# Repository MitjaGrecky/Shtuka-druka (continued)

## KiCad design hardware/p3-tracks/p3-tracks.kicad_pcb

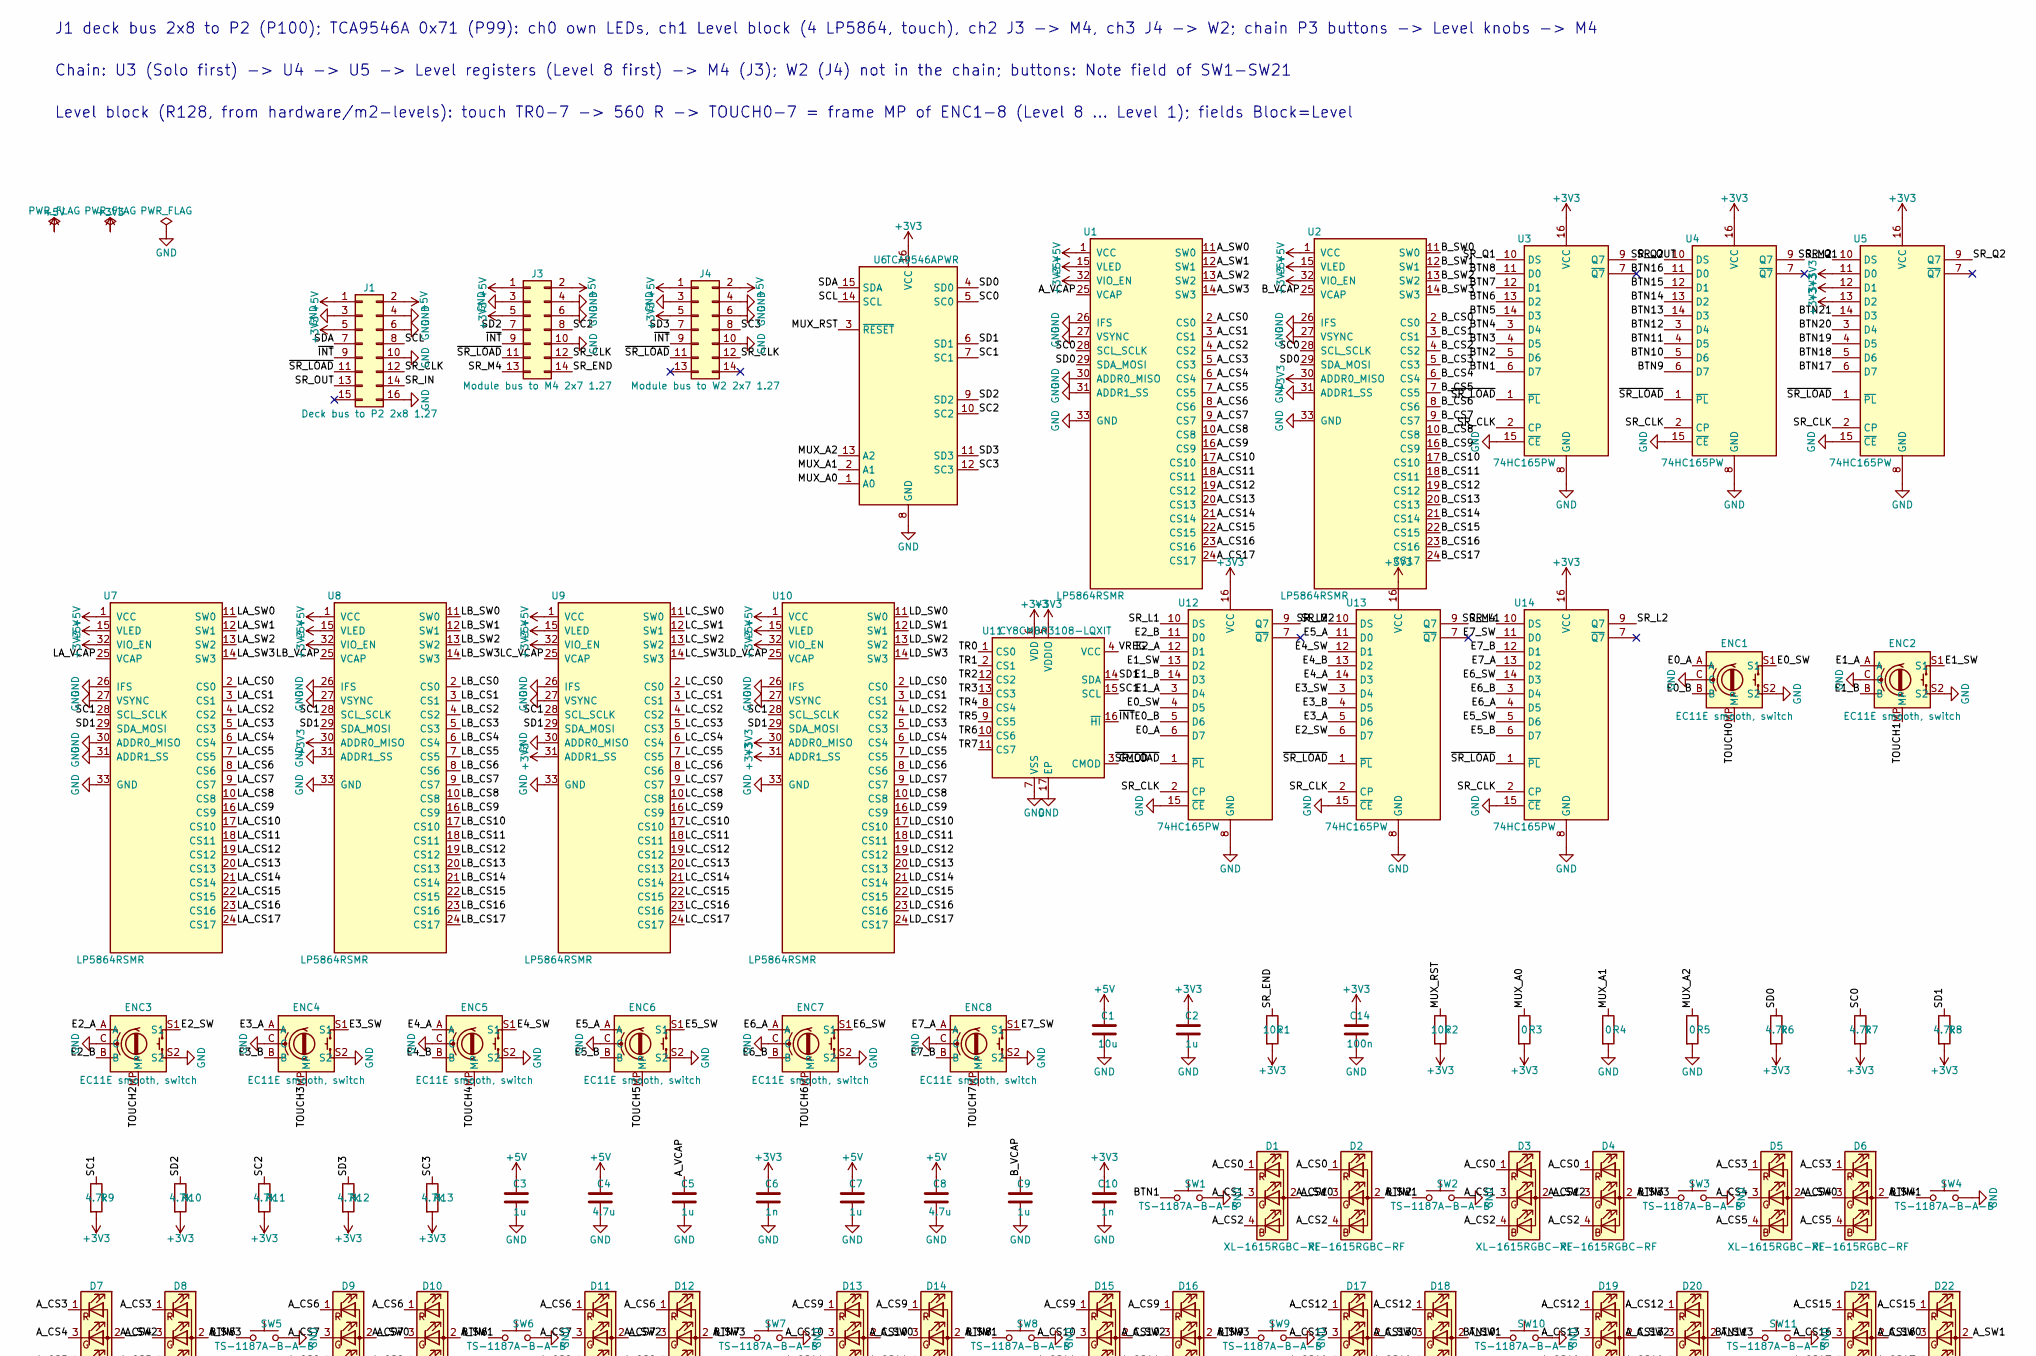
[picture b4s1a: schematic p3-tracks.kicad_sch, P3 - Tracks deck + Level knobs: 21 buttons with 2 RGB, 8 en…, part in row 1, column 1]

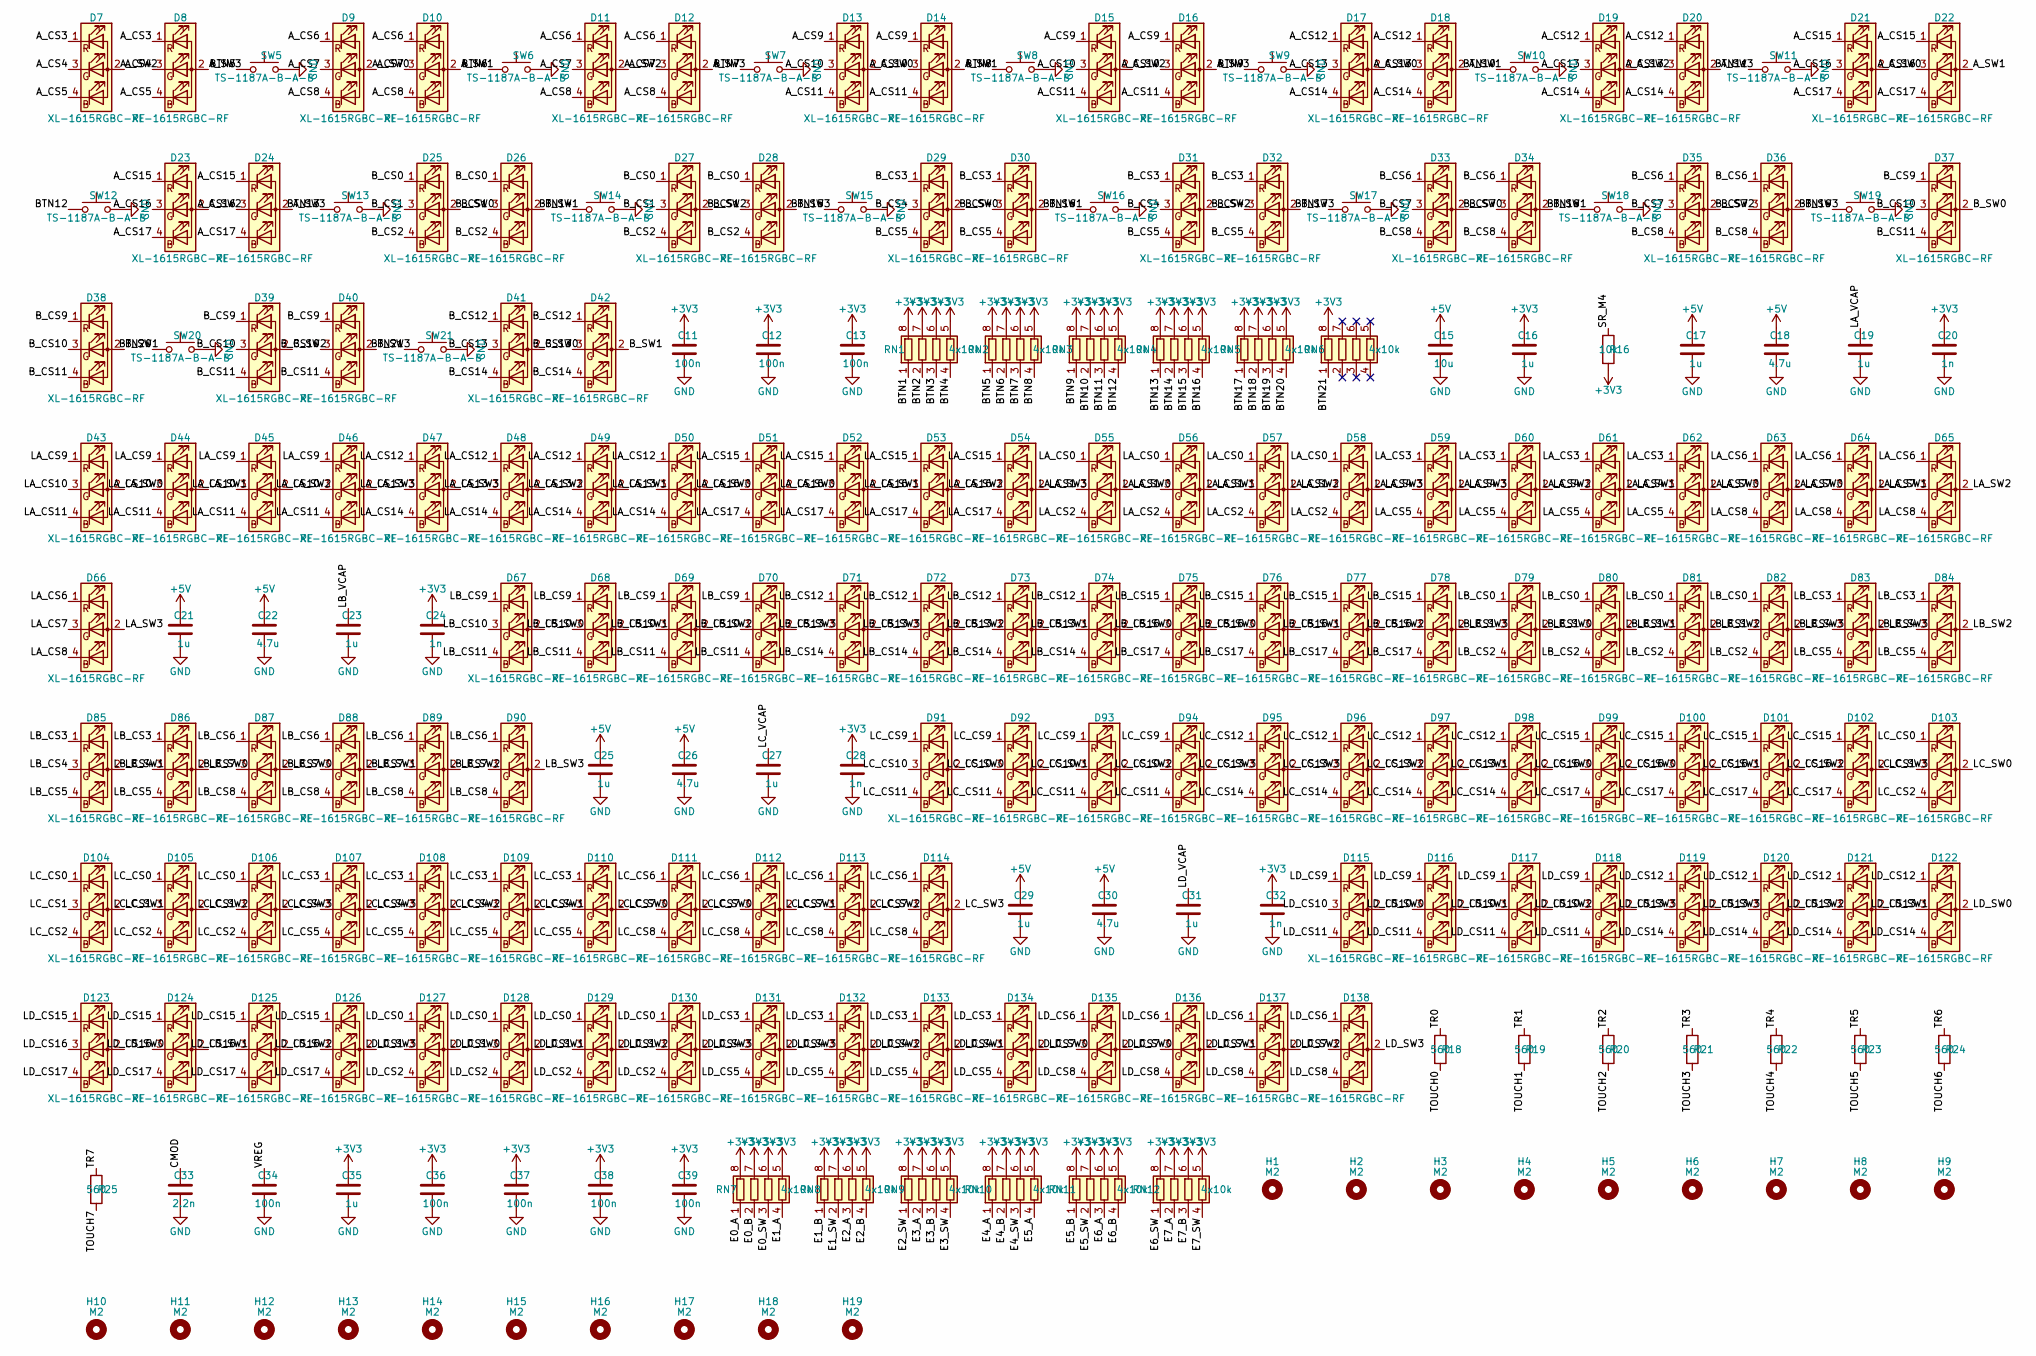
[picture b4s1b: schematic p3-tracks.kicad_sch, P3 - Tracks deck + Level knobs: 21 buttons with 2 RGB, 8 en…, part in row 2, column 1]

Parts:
C1, C15: 10u; C_0805_2012Metric; LCSC C15850
C2, C3, C5, C7, C9, C16, C17, C19, C21, C23, C25, C27, C29, C31, C35: 1u; C_0402_1005Metric; LCSC C52923
C4, C8, C18, C22, C26, C30: 4.7u; C_0805_2012Metric; LCSC C1779
C6, C10, C20, C24, C28, C32: 1n; C_0402_1005Metric; LCSC C1523
C11, C12, C13, C14, C34, C36, C37, C38, C39: 100n; C_0402_1005Metric; LCSC C1525
C33: 2.2n; C_0402_1005Metric; LCSC C1531
D1, D2, D3, D4, D5, D6, D7, D8, D9, D10, D11, D12, D13, D14, D15, D16, D17, D18, D19, D20, D21, D22, D23, D24, D25, D26, D27, D28, D29, D30, D31, D32, D33, D34, D35, D36, D37, D38, D39, D40, D41, D42, D43, D44, D45, D46, D47, D48, D49, D50, D51, D52, D53, D54, D55, D56, D57, D58, D59, D60, D61, D62, D63, D64, D65, D66, D67, D68, D69, D70, D71, D72, D73, D74, D75, D76, D77, D78, D79, D80, D81, D82, D83, D84, D85, D86, D87, D88, D89, D90, D91, D92, D93, D94, D95, D96, D97, D98, D99, D100, D101, D102, D103, D104, D105, D106, D107, D108, D109, D110, D111, D112, D113, D114, D115, D116, D117, D118, D119, D120, D121, D122, D123, D124, D125, D126, D127, D128, D129, D130, D131, D132, D133, D134, D135, D136, D137, D138: XL-1615RGBC-RF; LED_RGB_XL-1615RGBC_1.6x1.5mm; LCSC C965840
ENC1, ENC2, ENC3, ENC4, ENC5, ENC6, ENC7, ENC8: EC11E smooth, switch; RotaryEncoder_Alps_EC11E-Switch_Vertical_H20mm_Ring; LCSC C361165
H1, H2, H3, H4, H5, H6, H7, H8, H9, H10, H11, H12, H13, H14, H15, H16, H17, H18, H19: M2; MountingHole_2.2mm_M2
J1: Deck bus to P2 2x8 1.27; PinHeader_2x08_P1.27mm_Vertical; LCSC C5372812
J3: Module bus to M4 2x7 1.27; PinHeader_2x07_P1.27mm_Vertical; LCSC C5372811
J4: Module bus to W2 2x7 1.27; PinHeader_2x07_P1.27mm_Vertical; LCSC C5372811
R1, R2, R16: 10k; R_0402_1005Metric; LCSC C25744
R3, R4, R5: 0; R_0402_1005Metric; LCSC C17168
R6, R7, R8, R9, R10, R11, R12, R13: 4.7k; R_0402_1005Metric; LCSC C25900
R18, R19, R20, R21, R22, R23, R24, R25: 560; R_0402_1005Metric; LCSC C25126
RN1, RN2, RN3, RN4, RN5, RN6, RN7, RN8, RN9, RN10, RN11, RN12: 4x10k; R_Array_Convex_4x0402; LCSC C25725
SW1, SW2, SW3, SW4, SW5, SW6, SW7, SW8, SW9, SW10, SW11, SW12, SW13, SW14, SW15, SW16, SW17, SW18, SW19, SW20, SW21: TS-1187A-B-A-B; SW_Push_1P1T_XKB_TS-1187A; LCSC C318884
U1, U2, U7, U8, U9, U10: LP5864RSMR; VQFN-32-1EP_4x4mm_P0.4mm_EP2.8x2.8mm; LCSC C5220564
U3, U4, U5, U12, U13, U14: 74HC165PW; TSSOP-16_4.4x5mm_P0.65mm; LCSC C80696
U6: TCA9546APWR; TSSOP-16_4.4x5mm_P0.65mm; LCSC C201653
U11: CY8CMBR3108-LQXIT; QFN-16-1EP_3x3mm_P0.5mm_EP1.7x1.7mm; LCSC C462528

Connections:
+3V3: C2.1, C6.1, C10.1, C11.1, C12.1, C13.1, C14.1, C16.1, C20.1, C24.1, C28.1, C32.1, C35.1, C36.1, C37.1, C38.1, C39.1, J1.5, J3.5, J4.5, R1.2, R2.2, R3.2, R6.2, R7.2, R8.2, R9.2, R10.2, R11.2, R12.2, R13.2, R16.2, RN1.5 (R4.2), RN1.6 (R3.2), RN1.7 (R2.2), RN1.8 (R1.2), RN2.5 (R4.2), RN2.6 (R3.2), RN2.7 (R2.2), RN2.8 (R1.2), RN3.5 (R4.2), RN3.6 (R3.2), RN3.7 (R2.2), RN3.8 (R1.2), RN4.5 (R4.2), RN4.6 (R3.2), RN4.7 (R2.2), RN4.8 (R1.2), RN5.5 (R4.2), RN5.6 (R3.2), RN5.7 (R2.2), RN5.8 (R1.2), RN6.8 (R1.2), RN7.5 (R4.2), RN7.6 (R3.2), RN7.7 (R2.2), RN7.8 (R1.2), RN8.5 (R4.2), RN8.6 (R3.2), RN8.7 (R2.2), RN8.8 (R1.2), RN9.5 (R4.2), RN9.6 (R3.2), RN9.7 (R2.2), RN9.8 (R1.2), RN10.5 (R4.2), RN10.6 (R3.2), RN10.7 (R2.2), RN10.8 (R1.2), RN11.5 (R4.2), RN11.6 (R3.2), RN11.7 (R2.2), RN11.8 (R1.2), RN12.5 (R4.2), RN12.6 (R3.2), RN12.7 (R2.2), RN12.8 (R1.2), U1.32 (VIO_EN), U2.30 (ADDR0_MISO), U2.32 (VIO_EN), U3.16 (VCC), U4.16 (VCC), U5.11 (D0), U5.12 (D1), U5.13 (D2), U5.16 (VCC), U6.16 (VCC), U7.32 (VIO_EN), U8.30 (ADDR0_MISO), U8.32 (VIO_EN), U9.31 (ADDR1_SS), U9.32 (VIO_EN), U10.30 (ADDR0_MISO), U10.31 (ADDR1_SS), U10.32 (VIO_EN), U11.5 (VDDIO), U11.6 (VDD), U12.16 (VCC), U13.16 (VCC), U14.16 (VCC)
+5V: C1.1, C3.1, C4.1, C7.1, C8.1, C15.1, C17.1, C18.1, C21.1, C22.1, C25.1, C26.1, C29.1, C30.1, J1.1, J1.2, J3.1, J3.2, J4.1, J4.2, U1.1 (VCC), U1.15 (VLED), U2.1 (VCC), U2.15 (VLED), U7.1 (VCC), U7.15 (VLED), U8.1 (VCC), U8.15 (VLED), U9.1 (VCC), U9.15 (VLED), U10.1 (VCC), U10.15 (VLED)
/A_CS0: D1.1 (RK), D2.1 (RK), D3.1 (RK), D4.1 (RK), U1.2 (CS0)
/A_CS1: D1.3 (GK), D2.3 (GK), D3.3 (GK), D4.3 (GK), U1.3 (CS1)
/A_CS2: D1.4 (BK), D2.4 (BK), D3.4 (BK), D4.4 (BK), U1.4 (CS2)
/A_CS3: D5.1 (RK), D6.1 (RK), D7.1 (RK), D8.1 (RK), U1.5 (CS3)
/A_CS4: D5.3 (GK), D6.3 (GK), D7.3 (GK), D8.3 (GK), U1.6 (CS4)
/A_CS5: D5.4 (BK), D6.4 (BK), D7.4 (BK), D8.4 (BK), U1.7 (CS5)
/A_CS6: D9.1 (RK), D10.1 (RK), D11.1 (RK), D12.1 (RK), U1.8 (CS6)
/A_CS7: D9.3 (GK), D10.3 (GK), D11.3 (GK), D12.3 (GK), U1.9 (CS7)
/A_CS8: D9.4 (BK), D10.4 (BK), D11.4 (BK), D12.4 (BK), U1.10 (CS8)
/A_CS9: D13.1 (RK), D14.1 (RK), D15.1 (RK), D16.1 (RK), U1.16 (CS9)
/A_CS10: D13.3 (GK), D14.3 (GK), D15.3 (GK), D16.3 (GK), U1.17 (CS10)
/A_CS11: D13.4 (BK), D14.4 (BK), D15.4 (BK), D16.4 (BK), U1.18 (CS11)
/A_CS12: D17.1 (RK), D18.1 (RK), D19.1 (RK), D20.1 (RK), U1.19 (CS12)
/A_CS13: D17.3 (GK), D18.3 (GK), D19.3 (GK), D20.3 (GK), U1.20 (CS13)
/A_CS14: D17.4 (BK), D18.4 (BK), D19.4 (BK), D20.4 (BK), U1.21 (CS14)
/A_CS15: D21.1 (RK), D22.1 (RK), D23.1 (RK), D24.1 (RK), U1.22 (CS15)
/A_CS16: D21.3 (GK), D22.3 (GK), D23.3 (GK), D24.3 (GK), U1.23 (CS16)
/A_CS17: D21.4 (BK), D22.4 (BK), D23.4 (BK), D24.4 (BK), U1.24 (CS17)
/A_SW0: D1.2 (A), D5.2 (A), D9.2 (A), D13.2 (A), D17.2 (A), D21.2 (A), U1.11 (SW0)
/A_SW1: D2.2 (A), D6.2 (A), D10.2 (A), D14.2 (A), D18.2 (A), D22.2 (A), U1.12 (SW1)
/A_SW2: D3.2 (A), D7.2 (A), D11.2 (A), D15.2 (A), D19.2 (A), D23.2 (A), U1.13 (SW2)
/A_SW3: D4.2 (A), D8.2 (A), D12.2 (A), D16.2 (A), D20.2 (A), D24.2 (A), U1.14 (SW3)
/A_VCAP: C5.1, U1.25 (VCAP)
/BTN1: RN1.1 (R1.1), SW1.1, U3.6 (D7)
/BTN2: RN1.2 (R2.1), SW2.1, U3.5 (D6)
/BTN3: RN1.3 (R3.1), SW3.1, U3.4 (D5)
/BTN4: RN1.4 (R4.1), SW4.1, U3.3 (D4)
/BTN5: RN2.1 (R1.1), SW5.1, U3.14 (D3)
/BTN6: RN2.2 (R2.1), SW6.1, U3.13 (D2)
/BTN7: RN2.3 (R3.1), SW7.1, U3.12 (D1)
/BTN8: RN2.4 (R4.1), SW8.1, U3.11 (D0)
/BTN9: RN3.1 (R1.1), SW9.1, U4.6 (D7)
/BTN10: RN3.2 (R2.1), SW10.1, U4.5 (D6)
/BTN11: RN3.3 (R3.1), SW11.1, U4.4 (D5)
/BTN12: RN3.4 (R4.1), SW12.1, U4.3 (D4)
/BTN13: RN4.1 (R1.1), SW13.1, U4.14 (D3)
/BTN14: RN4.2 (R2.1), SW14.1, U4.13 (D2)
/BTN15: RN4.3 (R3.1), SW15.1, U4.12 (D1)
/BTN16: RN4.4 (R4.1), SW16.1, U4.11 (D0)
/BTN17: RN5.1 (R1.1), SW17.1, U5.6 (D7)
/BTN18: RN5.2 (R2.1), SW18.1, U5.5 (D6)
/BTN19: RN5.3 (R3.1), SW19.1, U5.4 (D5)
/BTN20: RN5.4 (R4.1), SW20.1, U5.3 (D4)
/BTN21: RN6.1 (R1.1), SW21.1, U5.14 (D3)
/B_CS0: D25.1 (RK), D26.1 (RK), D27.1 (RK), D28.1 (RK), U2.2 (CS0)
/B_CS1: D25.3 (GK), D26.3 (GK), D27.3 (GK), D28.3 (GK), U2.3 (CS1)
/B_CS2: D25.4 (BK), D26.4 (BK), D27.4 (BK), D28.4 (BK), U2.4 (CS2)
/B_CS3: D29.1 (RK), D30.1 (RK), D31.1 (RK), D32.1 (RK), U2.5 (CS3)
/B_CS4: D29.3 (GK), D30.3 (GK), D31.3 (GK), D32.3 (GK), U2.6 (CS4)
/B_CS5: D29.4 (BK), D30.4 (BK), D31.4 (BK), D32.4 (BK), U2.7 (CS5)
/B_CS6: D33.1 (RK), D34.1 (RK), D35.1 (RK), D36.1 (RK), U2.8 (CS6)
/B_CS7: D33.3 (GK), D34.3 (GK), D35.3 (GK), D36.3 (GK), U2.9 (CS7)
/B_CS8: D33.4 (BK), D34.4 (BK), D35.4 (BK), D36.4 (BK), U2.10 (CS8)
/B_CS9: D37.1 (RK), D38.1 (RK), D39.1 (RK), D40.1 (RK), U2.16 (CS9)
/B_CS10: D37.3 (GK), D38.3 (GK), D39.3 (GK), D40.3 (GK), U2.17 (CS10)
/B_CS11: D37.4 (BK), D38.4 (BK), D39.4 (BK), D40.4 (BK), U2.18 (CS11)
/B_CS12: D41.1 (RK), D42.1 (RK), U2.19 (CS12)
/B_CS13: D41.3 (GK), D42.3 (GK), U2.20 (CS13)
/B_CS14: D41.4 (BK), D42.4 (BK), U2.21 (CS14)
/B_CS15: U2.22 (CS15)
/B_CS16: U2.23 (CS16)
/B_CS17: U2.24 (CS17)
/B_SW0: D25.2 (A), D29.2 (A), D33.2 (A), D37.2 (A), D41.2 (A), U2.11 (SW0)
/B_SW1: D26.2 (A), D30.2 (A), D34.2 (A), D38.2 (A), D42.2 (A), U2.12 (SW1)
/B_SW2: D27.2 (A), D31.2 (A), D35.2 (A), D39.2 (A), U2.13 (SW2)
/B_SW3: D28.2 (A), D32.2 (A), D36.2 (A), D40.2 (A), U2.14 (SW3)
/B_VCAP: C9.1, U2.25 (VCAP)
/CMOD: C33.1, U11.3 (CMOD)
/E0_A: ENC1.A, RN7.1 (R1.1), U12.6 (D7)
/E0_B: ENC1.B, RN7.2 (R2.1), U12.5 (D6)
/E0_SW: ENC1.S1, RN7.3 (R3.1), U12.4 (D5)
/E1_A: ENC2.A, RN7.4 (R4.1), U12.3 (D4)
/E1_B: ENC2.B, RN8.1 (R1.1), U12.14 (D3)
/E1_SW: ENC2.S1, RN8.2 (R2.1), U12.13 (D2)
/E2_A: ENC3.A, RN8.3 (R3.1), U12.12 (D1)
/E2_B: ENC3.B, RN8.4 (R4.1), U12.11 (D0)
/E2_SW: ENC3.S1, RN9.1 (R1.1), U13.6 (D7)
/E3_A: ENC4.A, RN9.2 (R2.1), U13.5 (D6)
/E3_B: ENC4.B, RN9.3 (R3.1), U13.4 (D5)
/E3_SW: ENC4.S1, RN9.4 (R4.1), U13.3 (D4)
/E4_A: ENC5.A, RN10.1 (R1.1), U13.14 (D3)
/E4_B: ENC5.B, RN10.2 (R2.1), U13.13 (D2)
/E4_SW: ENC5.S1, RN10.3 (R3.1), U13.12 (D1)
/E5_A: ENC6.A, RN10.4 (R4.1), U13.11 (D0)
/E5_B: ENC6.B, RN11.1 (R1.1), U14.6 (D7)
/E5_SW: ENC6.S1, RN11.2 (R2.1), U14.5 (D6)
/E6_A: ENC7.A, RN11.3 (R3.1), U14.4 (D5)
/E6_B: ENC7.B, RN11.4 (R4.1), U14.3 (D4)
/E6_SW: ENC7.S1, RN12.1 (R1.1), U14.14 (D3)
/E7_A: ENC8.A, RN12.2 (R2.1), U14.13 (D2)
/E7_B: ENC8.B, RN12.3 (R3.1), U14.12 (D1)
/E7_SW: ENC8.S1, RN12.4 (R4.1), U14.11 (D0)
/LA_CS0: D55.1 (RK), D56.1 (RK), D57.1 (RK), D58.1 (RK), U7.2 (CS0)
/LA_CS1: D55.3 (GK), D56.3 (GK), D57.3 (GK), D58.3 (GK), U7.3 (CS1)
/LA_CS2: D55.4 (BK), D56.4 (BK), D57.4 (BK), D58.4 (BK), U7.4 (CS2)
/LA_CS3: D59.1 (RK), D60.1 (RK), D61.1 (RK), D62.1 (RK), U7.5 (CS3)
/LA_CS4: D59.3 (GK), D60.3 (GK), D61.3 (GK), D62.3 (GK), U7.6 (CS4)
/LA_CS5: D59.4 (BK), D60.4 (BK), D61.4 (BK), D62.4 (BK), U7.7 (CS5)
/LA_CS6: D63.1 (RK), D64.1 (RK), D65.1 (RK), D66.1 (RK), U7.8 (CS6)
/LA_CS7: D63.3 (GK), D64.3 (GK), D65.3 (GK), D66.3 (GK), U7.9 (CS7)
/LA_CS8: D63.4 (BK), D64.4 (BK), D65.4 (BK), D66.4 (BK), U7.10 (CS8)
/LA_CS9: D43.1 (RK), D44.1 (RK), D45.1 (RK), D46.1 (RK), U7.16 (CS9)
/LA_CS10: D43.3 (GK), D44.3 (GK), D45.3 (GK), D46.3 (GK), U7.17 (CS10)
/LA_CS11: D43.4 (BK), D44.4 (BK), D45.4 (BK), D46.4 (BK), U7.18 (CS11)
/LA_CS12: D47.1 (RK), D48.1 (RK), D49.1 (RK), D50.1 (RK), U7.19 (CS12)
/LA_CS13: D47.3 (GK), D48.3 (GK), D49.3 (GK), D50.3 (GK), U7.20 (CS13)
/LA_CS14: D47.4 (BK), D48.4 (BK), D49.4 (BK), D50.4 (BK), U7.21 (CS14)
/LA_CS15: D51.1 (RK), D52.1 (RK), D53.1 (RK), D54.1 (RK), U7.22 (CS15)
/LA_CS16: D51.3 (GK), D52.3 (GK), D53.3 (GK), D54.3 (GK), U7.23 (CS16)
/LA_CS17: D51.4 (BK), D52.4 (BK), D53.4 (BK), D54.4 (BK), U7.24 (CS17)
/LA_SW0: D43.2 (A), D50.2 (A), D51.2 (A), D55.2 (A), D62.2 (A), D63.2 (A), U7.11 (SW0)
/LA_SW1: D44.2 (A), D49.2 (A), D52.2 (A), D56.2 (A), D61.2 (A), D64.2 (A), U7.12 (SW1)
/LA_SW2: D45.2 (A), D48.2 (A), D53.2 (A), D57.2 (A), D60.2 (A), D65.2 (A), U7.13 (SW2)
/LA_SW3: D46.2 (A), D47.2 (A), D54.2 (A), D58.2 (A), D59.2 (A), D66.2 (A), U7.14 (SW3)
/LA_VCAP: C19.1, U7.25 (VCAP)
/LB_CS0: D79.1 (RK), D80.1 (RK), D81.1 (RK), D82.1 (RK), U8.2 (CS0)
/LB_CS1: D79.3 (GK), D80.3 (GK), D81.3 (GK), D82.3 (GK), U8.3 (CS1)
/LB_CS2: D79.4 (BK), D80.4 (BK), D81.4 (BK), D82.4 (BK), U8.4 (CS2)
/LB_CS3: D83.1 (RK), D84.1 (RK), D85.1 (RK), D86.1 (RK), U8.5 (CS3)
/LB_CS4: D83.3 (GK), D84.3 (GK), D85.3 (GK), D86.3 (GK), U8.6 (CS4)
/LB_CS5: D83.4 (BK), D84.4 (BK), D85.4 (BK), D86.4 (BK), U8.7 (CS5)
/LB_CS6: D87.1 (RK), D88.1 (RK), D89.1 (RK), D90.1 (RK), U8.8 (CS6)
/LB_CS7: D87.3 (GK), D88.3 (GK), D89.3 (GK), D90.3 (GK), U8.9 (CS7)
/LB_CS8: D87.4 (BK), D88.4 (BK), D89.4 (BK), D90.4 (BK), U8.10 (CS8)
/LB_CS9: D67.1 (RK), D68.1 (RK), D69.1 (RK), D70.1 (RK), U8.16 (CS9)
/LB_CS10: D67.3 (GK), D68.3 (GK), D69.3 (GK), D70.3 (GK), U8.17 (CS10)
/LB_CS11: D67.4 (BK), D68.4 (BK), D69.4 (BK), D70.4 (BK), U8.18 (CS11)
/LB_CS12: D71.1 (RK), D72.1 (RK), D73.1 (RK), D74.1 (RK), U8.19 (CS12)
/LB_CS13: D71.3 (GK), D72.3 (GK), D73.3 (GK), D74.3 (GK), U8.20 (CS13)
/LB_CS14: D71.4 (BK), D72.4 (BK), D73.4 (BK), D74.4 (BK), U8.21 (CS14)
/LB_CS15: D75.1 (RK), D76.1 (RK), D77.1 (RK), D78.1 (RK), U8.22 (CS15)
/LB_CS16: D75.3 (GK), D76.3 (GK), D77.3 (GK), D78.3 (GK), U8.23 (CS16)
/LB_CS17: D75.4 (BK), D76.4 (BK), D77.4 (BK), D78.4 (BK), U8.24 (CS17)
/LB_SW0: D67.2 (A), D74.2 (A), D75.2 (A), D79.2 (A), D86.2 (A), D87.2 (A), U8.11 (SW0)
/LB_SW1: D68.2 (A), D73.2 (A), D76.2 (A), D80.2 (A), D85.2 (A), D88.2 (A), U8.12 (SW1)
/LB_SW2: D69.2 (A), D72.2 (A), D77.2 (A), D81.2 (A), D84.2 (A), D89.2 (A), U8.13 (SW2)
/LB_SW3: D70.2 (A), D71.2 (A), D78.2 (A), D82.2 (A), D83.2 (A), D90.2 (A), U8.14 (SW3)
/LB_VCAP: C23.1, U8.25 (VCAP)
/LC_CS0: D103.1 (RK), D104.1 (RK), D105.1 (RK), D106.1 (RK), U9.2 (CS0)
/LC_CS1: D103.3 (GK), D104.3 (GK), D105.3 (GK), D106.3 (GK), U9.3 (CS1)
/LC_CS2: D103.4 (BK), D104.4 (BK), D105.4 (BK), D106.4 (BK), U9.4 (CS2)
/LC_CS3: D107.1 (RK), D108.1 (RK), D109.1 (RK), D110.1 (RK), U9.5 (CS3)
/LC_CS4: D107.3 (GK), D108.3 (GK), D109.3 (GK), D110.3 (GK), U9.6 (CS4)
/LC_CS5: D107.4 (BK), D108.4 (BK), D109.4 (BK), D110.4 (BK), U9.7 (CS5)
/LC_CS6: D111.1 (RK), D112.1 (RK), D113.1 (RK), D114.1 (RK), U9.8 (CS6)
/LC_CS7: D111.3 (GK), D112.3 (GK), D113.3 (GK), D114.3 (GK), U9.9 (CS7)
/LC_CS8: D111.4 (BK), D112.4 (BK), D113.4 (BK), D114.4 (BK), U9.10 (CS8)
/LC_CS9: D91.1 (RK), D92.1 (RK), D93.1 (RK), D94.1 (RK), U9.16 (CS9)
/LC_CS10: D91.3 (GK), D92.3 (GK), D93.3 (GK), D94.3 (GK), U9.17 (CS10)
/LC_CS11: D91.4 (BK), D92.4 (BK), D93.4 (BK), D94.4 (BK), U9.18 (CS11)
/LC_CS12: D95.1 (RK), D96.1 (RK), D97.1 (RK), D98.1 (RK), U9.19 (CS12)
/LC_CS13: D95.3 (GK), D96.3 (GK), D97.3 (GK), D98.3 (GK), U9.20 (CS13)
/LC_CS14: D95.4 (BK), D96.4 (BK), D97.4 (BK), D98.4 (BK), U9.21 (CS14)
/LC_CS15: D99.1 (RK), D100.1 (RK), D101.1 (RK), D102.1 (RK), U9.22 (CS15)
/LC_CS16: D99.3 (GK), D100.3 (GK), D101.3 (GK), D102.3 (GK), U9.23 (CS16)
/LC_CS17: D99.4 (BK), D100.4 (BK), D101.4 (BK), D102.4 (BK), U9.24 (CS17)
/LC_SW0: D91.2 (A), D98.2 (A), D99.2 (A), D103.2 (A), D110.2 (A), D111.2 (A), U9.11 (SW0)
/LC_SW1: D92.2 (A), D97.2 (A), D100.2 (A), D104.2 (A), D109.2 (A), D112.2 (A), U9.12 (SW1)
/LC_SW2: D93.2 (A), D96.2 (A), D101.2 (A), D105.2 (A), D108.2 (A), D113.2 (A), U9.13 (SW2)
/LC_SW3: D94.2 (A), D95.2 (A), D102.2 (A), D106.2 (A), D107.2 (A), D114.2 (A), U9.14 (SW3)
/LC_VCAP: C27.1, U9.25 (VCAP)
/LD_CS0: D127.1 (RK), D128.1 (RK), D129.1 (RK), D130.1 (RK), U10.2 (CS0)
/LD_CS1: D127.3 (GK), D128.3 (GK), D129.3 (GK), D130.3 (GK), U10.3 (CS1)
/LD_CS2: D127.4 (BK), D128.4 (BK), D129.4 (BK), D130.4 (BK), U10.4 (CS2)
/LD_CS3: D131.1 (RK), D132.1 (RK), D133.1 (RK), D134.1 (RK), U10.5 (CS3)
/LD_CS4: D131.3 (GK), D132.3 (GK), D133.3 (GK), D134.3 (GK), U10.6 (CS4)
/LD_CS5: D131.4 (BK), D132.4 (BK), D133.4 (BK), D134.4 (BK), U10.7 (CS5)
/LD_CS6: D135.1 (RK), D136.1 (RK), D137.1 (RK), D138.1 (RK), U10.8 (CS6)
/LD_CS7: D135.3 (GK), D136.3 (GK), D137.3 (GK), D138.3 (GK), U10.9 (CS7)
/LD_CS8: D135.4 (BK), D136.4 (BK), D137.4 (BK), D138.4 (BK), U10.10 (CS8)
/LD_CS9: D115.1 (RK), D116.1 (RK), D117.1 (RK), D118.1 (RK), U10.16 (CS9)
/LD_CS10: D115.3 (GK), D116.3 (GK), D117.3 (GK), D118.3 (GK), U10.17 (CS10)
/LD_CS11: D115.4 (BK), D116.4 (BK), D117.4 (BK), D118.4 (BK), U10.18 (CS11)
/LD_CS12: D119.1 (RK), D120.1 (RK), D121.1 (RK), D122.1 (RK), U10.19 (CS12)
/LD_CS13: D119.3 (GK), D120.3 (GK), D121.3 (GK), D122.3 (GK), U10.20 (CS13)
/LD_CS14: D119.4 (BK), D120.4 (BK), D121.4 (BK), D122.4 (BK), U10.21 (CS14)
/LD_CS15: D123.1 (RK), D124.1 (RK), D125.1 (RK), D126.1 (RK), U10.22 (CS15)
/LD_CS16: D123.3 (GK), D124.3 (GK), D125.3 (GK), D126.3 (GK), U10.23 (CS16)
/LD_CS17: D123.4 (BK), D124.4 (BK), D125.4 (BK), D126.4 (BK), U10.24 (CS17)
/LD_SW0: D115.2 (A), D122.2 (A), D123.2 (A), D127.2 (A), D134.2 (A), D135.2 (A), U10.11 (SW0)
/LD_SW1: D116.2 (A), D121.2 (A), D124.2 (A), D128.2 (A), D133.2 (A), D136.2 (A), U10.12 (SW1)
/LD_SW2: D117.2 (A), D120.2 (A), D125.2 (A), D129.2 (A), D132.2 (A), D137.2 (A), U10.13 (SW2)
/LD_SW3: D118.2 (A), D119.2 (A), D126.2 (A), D130.2 (A), D131.2 (A), D138.2 (A), U10.14 (SW3)
/LD_VCAP: C31.1, U10.25 (VCAP)
/MUX_A0: R3.1, U6.1 (A0)
/MUX_A1: R4.1, U6.2 (A1)
/MUX_A2: R5.1, U6.13 (A2)
/MUX_RST: R2.1, U6.3 (~RESET)
/SC0: R7.1, U1.28 (SCL_SCLK), U2.28 (SCL_SCLK), U6.5 (SC0)
/SC1: R9.1, U6.7 (SC1), U7.28 (SCL_SCLK), U8.28 (SCL_SCLK), U9.28 (SCL_SCLK), U10.28 (SCL_SCLK), U11.15 (SCL)
/SC2: J3.8, R11.1, U6.10 (SC2)
/SC3: J4.8, R13.1, U6.12 (SC3)
/SCL: J1.8, U6.14 (SCL)
/SD0: R6.1, U1.29 (SDA_MOSI), U2.29 (SDA_MOSI), U6.4 (SD0)
/SD1: R8.1, U6.6 (SD1), U7.29 (SDA_MOSI), U8.29 (SDA_MOSI), U9.29 (SDA_MOSI), U10.29 (SDA_MOSI), U11.14 (SDA)
/SD2: J3.7, R10.1, U6.9 (SD2)
/SD3: J4.7, R12.1, U6.11 (SD3)
/SDA: J1.7, U6.15 (SDA)
/SR_CLK: J1.12, J3.12, J4.12, U3.2 (CP), U4.2 (CP), U5.2 (CP), U12.2 (CP), U13.2 (CP), U14.2 (CP)
/SR_END: J3.14, R1.1
/SR_IN: J1.14
/SR_L1: U12.10 (DS), U13.9 (Q7)
/SR_L2: U13.10 (DS), U14.9 (Q7)
/SR_M2: U5.10 (DS), U12.9 (Q7)
/SR_M4: J3.13, R16.1, U14.10 (DS)
/SR_OUT: J1.13, U3.9 (Q7)
/SR_Q1: U3.10 (DS), U4.9 (Q7)
/SR_Q2: U4.10 (DS), U5.9 (Q7)
/TOUCH0: ENC1.MP, R18.2
/TOUCH1: ENC2.MP, R19.2
/TOUCH2: ENC3.MP, R20.2
/TOUCH3: ENC4.MP, R21.2
/TOUCH4: ENC5.MP, R22.2
/TOUCH5: ENC6.MP, R23.2
/TOUCH6: ENC7.MP, R24.2
/TOUCH7: ENC8.MP, R25.2
/TR0: R18.1, U11.1 (CS0)
/TR1: R19.1, U11.2 (CS1)
/TR2: R20.1, U11.12 (CS2)
/TR3: R21.1, U11.13 (CS3)
/TR4: R22.1, U11.8 (CS4)
/TR5: R23.1, U11.9 (CS5)
/TR6: R24.1, U11.10 (CS6)
/TR7: R25.1, U11.11 (CS7)
/VREG: C34.1, U11.4 (VCC)
/~INT: J1.9, J3.9, J4.9, U11.16 (~HI)
/~SR_LOAD: J1.11, J3.11, J4.11, U3.1 (~PL), U4.1 (~PL), U5.1 (~PL), U12.1 (~PL), U13.1 (~PL), U14.1 (~PL)
GND: C1.2, C2.2, C3.2, C4.2, C5.2, C6.2, C7.2, C8.2, C9.2, C10.2, C11.2, C12.2, C13.2, C14.2, C15.2, C16.2, C17.2, C18.2, C19.2, C20.2, C21.2, C22.2, C23.2, C24.2, C25.2, C26.2, C27.2, C28.2, C29.2, C30.2, C31.2, C32.2, C33.2, C34.2, C35.2, C36.2, C37.2, C38.2, C39.2, ENC1.C, ENC1.S2, ENC2.C, ENC2.S2, ENC3.C, ENC3.S2, ENC4.C, ENC4.S2, ENC5.C, ENC5.S2, ENC6.C, ENC6.S2, ENC7.C, ENC7.S2, ENC8.C, ENC8.S2, J1.3, J1.4, J1.6, J1.10, J1.16, J3.3, J3.4, J3.6, J3.10, J4.3, J4.4, J4.6, J4.10, R4.2, R5.2, SW1.2, SW2.2, SW3.2, SW4.2, SW5.2, SW6.2, SW7.2, SW8.2, SW9.2, SW10.2, SW11.2, SW12.2, SW13.2, SW14.2, SW15.2, SW16.2, SW17.2, SW18.2, SW19.2, SW20.2, SW21.2, U1.26 (IFS), U1.27 (VSYNC), U1.30 (ADDR0_MISO), U1.31 (ADDR1_SS), U1.33 (GND), U2.26 (IFS), U2.27 (VSYNC), U2.31 (ADDR1_SS), U2.33 (GND), U3.8 (GND), U3.15 (~CE), U4.8 (GND), U4.15 (~CE), U5.8 (GND), U5.15 (~CE), U6.8 (GND), U7.26 (IFS), U7.27 (VSYNC), U7.30 (ADDR0_MISO), U7.31 (ADDR1_SS), U7.33 (GND), U8.26 (IFS), U8.27 (VSYNC), U8.31 (ADDR1_SS), U8.33 (GND), U9.26 (IFS), U9.27 (VSYNC), U9.30 (ADDR0_MISO), U9.33 (GND), U10.26 (IFS), U10.27 (VSYNC), U10.33 (GND), U11.7 (VSS), U11.17 (EP), U12.8 (GND), U12.15 (~CE), U13.8 (GND), U13.15 (~CE), U14.8 (GND), U14.15 (~CE)

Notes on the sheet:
J1 deck bus 2x8 to P2 (P100); TCA9546A 0x71 (P99): ch0 own LEDs, ch1 Level block (4 LP5864, touch), ch2 J3 -> M4, ch3 J4 -> W2; chain P3 buttons -> Level knobs -> M4
Chain: U3 (Solo first) -> U4 -> U5 -> Level registers (Level 8 first) -> M4 (J3); W2 (J4) not in the chain; buttons: Note field of SW1-SW21
Level block (R128, from hardware/m2-levels): touch TR0-7 -> 560 R -> TOUCH0-7 = frame MP of ENC1-8 (Level 8 ... Level 1); fields Block=Level

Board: 4 copper layers, 276 parts (90 on the bottom side), 226 nets, no tracks yet.

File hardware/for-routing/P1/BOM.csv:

Comment,Designator,Footprint,LCSC Part #
Deck bus to P2 2x8 1.27,J1,PinHeader_2x08_P1.27mm_Vertical,C5372812
Module bus to M3 2x7 1.27,J2,PinHeader_2x07_P1.27mm_Vertical,C5372811
Module bus to W1 2x7 1.27,J3,PinHeader_2x07_P1.27mm_Vertical,C5372811
10u,C1,C_0805_2012Metric,C15850
1u,"C2,C3,C5,C7,C9",C_0402_1005Metric,C52923
10k,"R1,R2",R_0402_1005Metric,C25744
TCA9546APWR,U6,TSSOP-16_4.4x5mm_P0.65mm,C201653
100n,"C11,C12,C13,C14",C_0402_1005Metric,C1525
0,"R3,R4,R5",R_0402_1005Metric,C17168
4.7k,"R6,R7,R8,R9,R10,R11",R_0402_1005Metric,C25900
LP5864RSMR,"U1,U2",VQFN-32-1EP_4x4mm_P0.4mm_EP2.8x2.8mm,C5220564
4.7u,"C4,C8",C_0805_2012Metric,C1779
1n,"C6,C10",C_0402_1005Metric,C1523
TS-1187A-B-A-B,"SW1,SW2,SW3,SW4,SW5,SW6,SW7,SW8,SW9,SW10,SW11,SW12,SW13,SW14,SW15,SW16,SW17,SW18,SW19",SW_Push_1P1T_XKB_TS-1187A,C318884
XL-1615RGBC-RF,"D1,D2,D3,D4,D5,D6,D7,D8,D9,D10,D11,D12,D13,D14,D15,D16,D17,D18,D19,D20,D21,D22,D23,D24,D25,D26,D27,D28,D29,D30,D31,D32,D33,D34,D35,D36,D37,D38",LED_RGB_XL-1615RGBC_1.6x1.5mm,C965840
74HC165PW,"U3,U4,U5",TSSOP-16_4.4x5mm_P0.65mm,C80696
4x10k,"RN1,RN2,RN3,RN4,RN5",R_Array_Convex_4x0402,C25725

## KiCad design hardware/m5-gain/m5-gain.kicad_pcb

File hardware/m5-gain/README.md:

# M5 - Gain 1 + 2 (encoder module on the slope, in W1's window)

Two smooth encoders with push (Gain 1, Gain 2), rings of 11 RGB LEDs and the two Clip LEDs - 24 RGB on one LP5864 (P103).
Spec: `hardware/for-routing/SPEC_boards.md`, section M5; W1: `hardware/w1-levels`. Status: rev 0.2 (V1 board to panel x 99, V2 rings r 10.5) - schematic and placed board,
not routed (`UNROUTED`). Package: `hardware/for-routing/M5/`.

| | |
|---|---|
| Board | 84 x 34 mm, 2 layers; panel x 15-99 (V1, user 13.11; W1 board x 5-89 - W1's window is widened by the cloud, its window `M5_X`), centred on the Gain row along the slope |
| Top side | 2 x EC11E (panel x 32 and 80, y 379; knob 16 mm), 22 x XL-1615RGBC-RF on rings r 10.5 mm (layout ring 21, V2) (11 per ring), Clip 1 and Clip 2 (x 48 and 96, y 386) |
| Bottom side | LP5864, 74HC165, 2 x 4x10k, passives between the knobs, J1 at the front edge at x 41 (opposite W1's J2) |
| Bus | J1 2 x 7, 1.27 mm to W1's J2; W1 passes the bus on (I2C channel 2 of P1's TCA9546A; W1 has 0x48, 0x54) |
| I2C | LP5864 0x40 |
| LEDs | Gain 1 ring + Clip 1 on CS9-17, Gain 2 ring + Clip 2 on CS0-8; each Clip LED is the 12th position of its ring's triples |
| Shift chain | D7..D0: Gain 1 A, B, push, Gain 2 A, B, push, 1, 1 (W1 reads M5 after its own P48 buttons) |
| Holes | M2 in the corners and one in the middle of the rear edge |

Checks (12.11.2026, KiCad 10.0.8): ERC 0 errors; netlist 202 pins, 0 mismatches; parity 0, 163 unrouted;
**DRC 2 errors: Clip 2 (D24) pads 0.15 mm from the right edge (rule 0.3)** - the LED sits at panel x 96, the board ends at 97.
EasyEDA Pro import (project M5_v2, rev 0.2; Clip 2 now 3 mm from the edge): PCB 38/38, schematic 38/38 nets, 46/46 parts.

Open questions (notes/handoff.md): Clip 2 at the edge (widen M5 and W1's window to panel x 99, or move Clip 2 to x 94);
ring radius: V2 (user 13.11) - the layout's ring (21 mm) wins over the spec formula (r 11): r 10.5 mm.

Generators: `gen/design.py`, `gen/make_sch.py`, `gen/check_netlist.py`, `gen/make_pcb.py` (shared writers in `hardware/common/gen`).
PC (KiCad 10) in one go: `powershell -File hardware/common/gen/run_board.ps1 m5-gain M5`.

License: CERN-OHL-S-2.0 (hardware), AGPL-3.0-or-later (scripts).

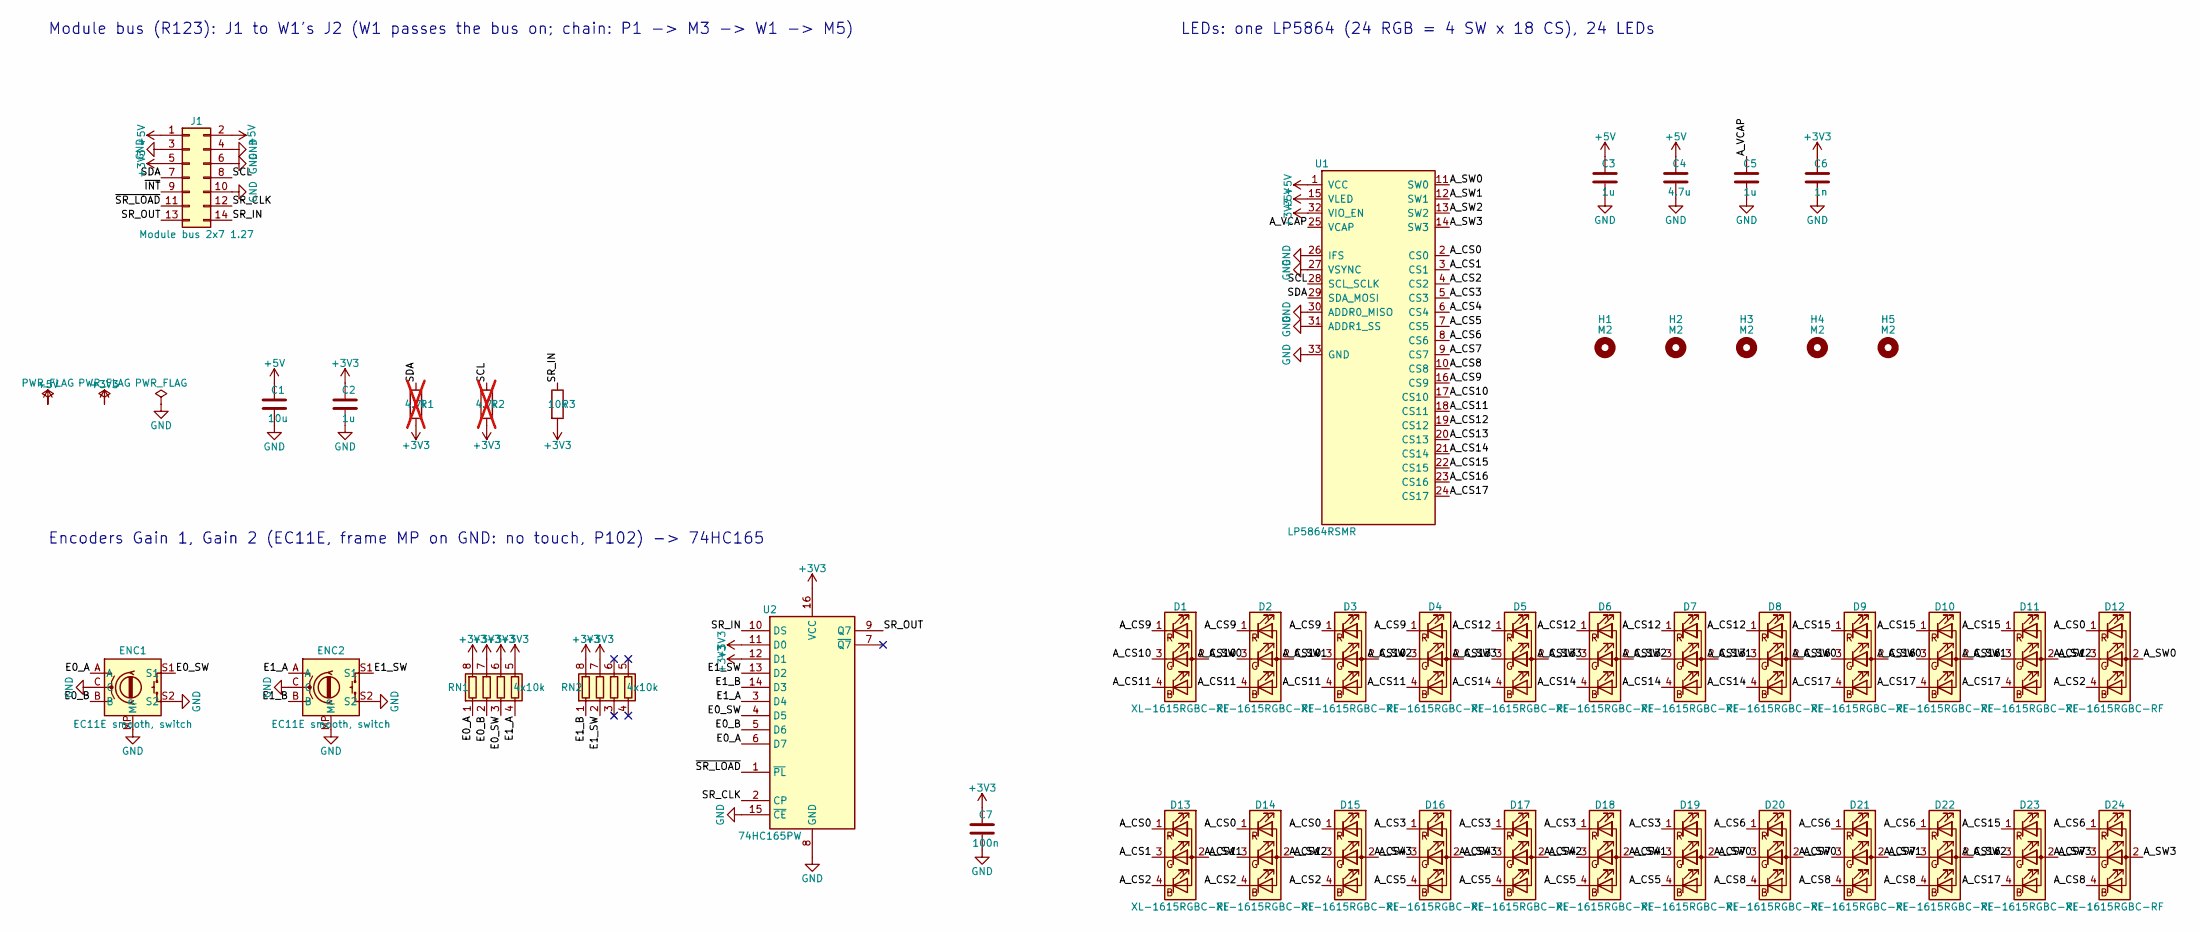
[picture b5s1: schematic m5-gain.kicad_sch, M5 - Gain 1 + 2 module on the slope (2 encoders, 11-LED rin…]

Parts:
C1: 10u; C_0805_2012Metric; LCSC C15850
C2, C3, C5: 1u; C_0402_1005Metric; LCSC C52923
C4: 4.7u; C_0805_2012Metric; LCSC C1779
C6: 1n; C_0402_1005Metric; LCSC C1523
C7: 100n; C_0402_1005Metric; LCSC C1525
D1, D2, D3, D4, D5, D6, D7, D8, D9, D10, D11, D12, D13, D14, D15, D16, D17, D18, D19, D20, D21, D22, D23, D24: XL-1615RGBC-RF; LED_RGB_XL-1615RGBC_1.6x1.5mm; LCSC C965840
ENC1, ENC2: EC11E smooth, switch; RotaryEncoder_Alps_EC11E-Switch_Vertical_H20mm_Ring; LCSC C361165
H1, H2, H3, H4, H5: M2; MountingHole_2.2mm_M2
J1: Module bus 2x7 1.27; PinHeader_2x07_P1.27mm_Vertical; LCSC C5372811
R1, R2: 4.7k; R_0402_1005Metric; LCSC C25900; not fitted
R3: 10k; R_0402_1005Metric; LCSC C25744
RN1, RN2: 4x10k; R_Array_Convex_4x0402; LCSC C25725
U1: LP5864RSMR; VQFN-32-1EP_4x4mm_P0.4mm_EP2.8x2.8mm; LCSC C5220564
U2: 74HC165PW; TSSOP-16_4.4x5mm_P0.65mm; LCSC C80696

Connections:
+3V3: C2.1, C6.1, C7.1, J1.5, R1.2, R2.2, R3.2, RN1.5 (R4.2), RN1.6 (R3.2), RN1.7 (R2.2), RN1.8 (R1.2), RN2.7 (R2.2), RN2.8 (R1.2), U1.32 (VIO_EN), U2.11 (D0), U2.12 (D1), U2.16 (VCC)
+5V: C1.1, C3.1, C4.1, J1.1, J1.2, U1.1 (VCC), U1.15 (VLED)
/A_CS0: D12.1 (RK), D13.1 (RK), D14.1 (RK), D15.1 (RK), U1.2 (CS0)
/A_CS1: D12.3 (GK), D13.3 (GK), D14.3 (GK), D15.3 (GK), U1.3 (CS1)
/A_CS2: D12.4 (BK), D13.4 (BK), D14.4 (BK), D15.4 (BK), U1.4 (CS2)
/A_CS3: D16.1 (RK), D17.1 (RK), D18.1 (RK), D19.1 (RK), U1.5 (CS3)
/A_CS4: D16.3 (GK), D17.3 (GK), D18.3 (GK), D19.3 (GK), U1.6 (CS4)
/A_CS5: D16.4 (BK), D17.4 (BK), D18.4 (BK), D19.4 (BK), U1.7 (CS5)
/A_CS6: D20.1 (RK), D21.1 (RK), D22.1 (RK), D24.1 (RK), U1.8 (CS6)
/A_CS7: D20.3 (GK), D21.3 (GK), D22.3 (GK), D24.3 (GK), U1.9 (CS7)
/A_CS8: D20.4 (BK), D21.4 (BK), D22.4 (BK), D24.4 (BK), U1.10 (CS8)
/A_CS9: D1.1 (RK), D2.1 (RK), D3.1 (RK), D4.1 (RK), U1.16 (CS9)
/A_CS10: D1.3 (GK), D2.3 (GK), D3.3 (GK), D4.3 (GK), U1.17 (CS10)
/A_CS11: D1.4 (BK), D2.4 (BK), D3.4 (BK), D4.4 (BK), U1.18 (CS11)
/A_CS12: D5.1 (RK), D6.1 (RK), D7.1 (RK), D8.1 (RK), U1.19 (CS12)
/A_CS13: D5.3 (GK), D6.3 (GK), D7.3 (GK), D8.3 (GK), U1.20 (CS13)
/A_CS14: D5.4 (BK), D6.4 (BK), D7.4 (BK), D8.4 (BK), U1.21 (CS14)
/A_CS15: D9.1 (RK), D10.1 (RK), D11.1 (RK), D23.1 (RK), U1.22 (CS15)
/A_CS16: D9.3 (GK), D10.3 (GK), D11.3 (GK), D23.3 (GK), U1.23 (CS16)
/A_CS17: D9.4 (BK), D10.4 (BK), D11.4 (BK), D23.4 (BK), U1.24 (CS17)
/A_SW0: D1.2 (A), D8.2 (A), D9.2 (A), D12.2 (A), D19.2 (A), D20.2 (A), U1.11 (SW0)
/A_SW1: D2.2 (A), D7.2 (A), D10.2 (A), D13.2 (A), D18.2 (A), D21.2 (A), U1.12 (SW1)
/A_SW2: D3.2 (A), D6.2 (A), D11.2 (A), D14.2 (A), D17.2 (A), D22.2 (A), U1.13 (SW2)
/A_SW3: D4.2 (A), D5.2 (A), D15.2 (A), D16.2 (A), D23.2 (A), D24.2 (A), U1.14 (SW3)
/A_VCAP: C5.1, U1.25 (VCAP)
/E0_A: ENC1.A, RN1.1 (R1.1), U2.6 (D7)
/E0_B: ENC1.B, RN1.2 (R2.1), U2.5 (D6)
/E0_SW: ENC1.S1, RN1.3 (R3.1), U2.4 (D5)
/E1_A: ENC2.A, RN1.4 (R4.1), U2.3 (D4)
/E1_B: ENC2.B, RN2.1 (R1.1), U2.14 (D3)
/E1_SW: ENC2.S1, RN2.2 (R2.1), U2.13 (D2)
/SCL: J1.8, R2.1, U1.28 (SCL_SCLK)
/SDA: J1.7, R1.1, U1.29 (SDA_MOSI)
/SR_CLK: J1.12, U2.2 (CP)
/SR_IN: J1.14, R3.1, U2.10 (DS)
/SR_OUT: J1.13, U2.9 (Q7)
/~INT: J1.9
/~SR_LOAD: J1.11, U2.1 (~PL)
GND: C1.2, C2.2, C3.2, C4.2, C5.2, C6.2, C7.2, ENC1.C, ENC1.MP, ENC1.S2, ENC2.C, ENC2.MP, ENC2.S2, J1.3, J1.4, J1.6, J1.10, U1.26 (IFS), U1.27 (VSYNC), U1.30 (ADDR0_MISO), U1.31 (ADDR1_SS), U1.33 (GND), U2.8 (GND), U2.15 (~CE)

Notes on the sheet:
Module bus (R123): J1 to W1's J2 (W1 passes the bus on; chain: P1 -> M3 -> W1 -> M5)
Encoders Gain 1, Gain 2 (EC11E, frame MP on GND: no touch, P102) -> 74HC165
LEDs: one LP5864 (24 RGB = 4 SW x 18 CS), 24 LEDs

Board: 2 copper layers, 46 parts (15 on the bottom side), 38 nets, no tracks yet.

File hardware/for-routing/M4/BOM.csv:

Comment,Designator,Footprint,LCSC Part #
Module bus 2x7 1.27,J1,PinHeader_2x07_P1.27mm_Vertical,C5372811
10u,C1,C_0805_2012Metric,C15850
1u,"C2,C3,C5",C_0402_1005Metric,C52923
10k,R3,R_0402_1005Metric,C25744
LP5864RSMR,U1,VQFN-32-1EP_4x4mm_P0.4mm_EP2.8x2.8mm,C5220564
4.7u,C4,C_0805_2012Metric,C1779
1n,C6,C_0402_1005Metric,C1523
XL-1615RGBC-RF,"D1,D2,D3,D4,D5,D6,D7,D8,D9,D10,D11,D12,D13,D14,D15,D16,D17,D18,D19,D20,D21,D22,D23,D24",LED_RGB_XL-1615RGBC_1.6x1.5mm,C965840
74HC165PW,U2,TSSOP-16_4.4x5mm_P0.65mm,C80696
100n,C7,C_0402_1005Metric,C1525
4x10k,"RN1,RN2",R_Array_Convex_4x0402,C25725
"EC11E smooth, switch","ENC1,ENC2",RotaryEncoder_Alps_EC11E-Switch_Vertical_H20mm_Ring,C361165
